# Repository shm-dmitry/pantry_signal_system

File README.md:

This is signal system for pantry.
It will control climate of pantry to smart house.

It will uses autonomous power system
1. car battery on 12v
2. temporary Li-Ion battary on 12v for charging primary battery
3. internal battery (6V..15V) which will used in case of primary and reserve 12V battery discharged. Used to send power alarm to smart house
4. Auto battary hot switch
5. Control over-discharge of all batteries
6. Provide information of current voltage to controller
7. Small current consumption. I plan to charge main battary once per ~6 month. 

It will collect and send next information (incl alarms):
1. Inside flooding alarm
2. Outside flooding alarm
3. Inside humidity level
4. Inside temperature
5. Inside light level
6. Open door alarm
7. Current voltage of all batteries
8. Current battery in use
9. Both 12V batteries discharged alarm 

It will automatically switch on air-drier basing on humidity level

It will have air fan system
1. Manual swotch on
2. Manual swotch off
3. Auto switch off after ~20 minutes

It will send all collected information to smart house system using LoRa channel

Project status

| Hardware | Status |
| --- | --- |
| Supply module | OK |
| Supply module :: Supply controller | OK |
| Logic module :: Flooding sensors | OK |
| Logic module :: Light sensor | OK |
| Logic module :: display | OK |
| Logic module :: humidity and temperature | OK |
| Logic module :: air dryer | OK |
| Logic module :: LoRa transmitter | OK |
| Logic module :: Open door alarm | OK |
| Logic module :: Wakeup button | OK |
| Air fan module | OK |
| LoRa receiver and smart house integration | OK |

| Firmware | Status |
| --- | --- |
| Supply controller | OK |
| Logic controller :: flooding sensors | OK |
| Logic controller :: light sensor | OK |
| Logic controller :: display | OK |
| Logic controller :: humidity and temperature | OK |
| Logic controller :: air dryer | OK |
| Logic controller :: LoRa transmitter | OK |
| Logic controller :: Open door alarm | OK |
| Logic controller :: Wakeup button and deep sleep mode | OK |
| Logic controller :: Integration with supply controller | OK |
| LoRa receiver and smart house integration | OK |

| Board | Status |
| --- | --- |
| Supply board | OK |
| logic module board | OK |
| fan board | OK |
| LoRa Receiver | OK |

| 3D models | Status |
| --- | --- |
| Supply board box | OK |
| Logic model box | OK |
| Air dryer | OK |
| Fan box | OK |
| Fan air intake | OK |
| LoRa receiver box | no |

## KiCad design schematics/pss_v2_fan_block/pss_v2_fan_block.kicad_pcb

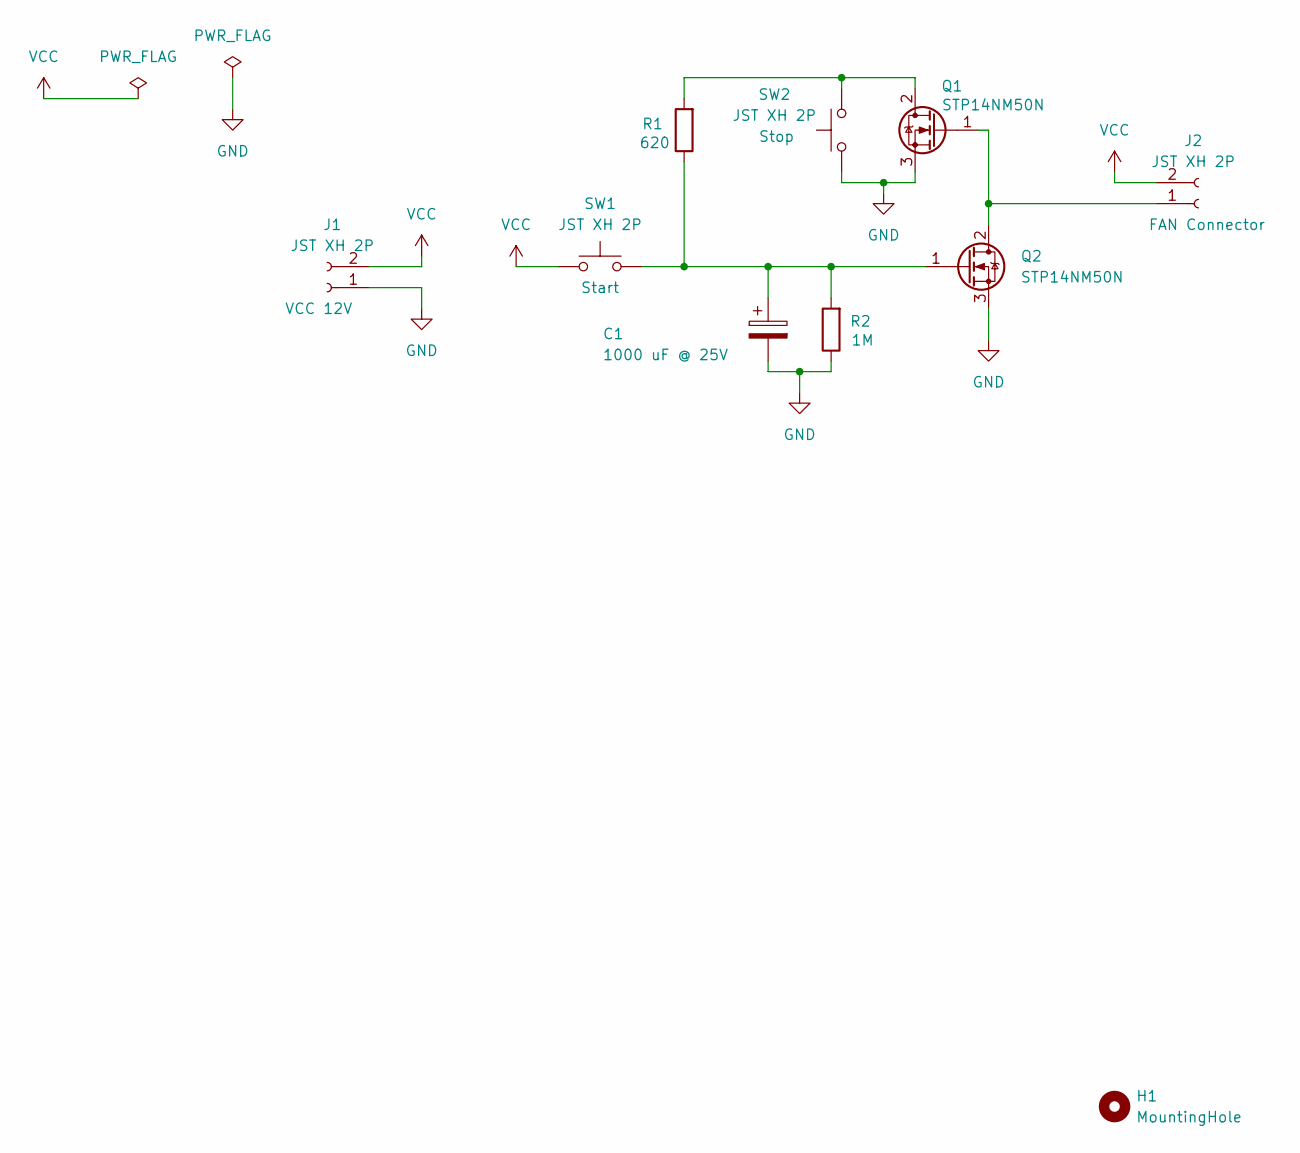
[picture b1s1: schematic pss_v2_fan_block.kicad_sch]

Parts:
C1: 1000 uF @ 25V; CP_Radial_D10.0mm_P5.00mm
H1: MountingHole; MountingHole_2.2mm_M2
J1, J2: JST XH 2P; JST_XH_B2B-XH-A_1x02_P2.50mm_Vertical
Q1, Q2: STP14NM50N; TO-220-3_Vertical
R1: 620; R_0805_2012Metric
R2: 1M; R_0805_2012Metric
SW1, SW2: JST XH 2P; JST_XH_B2B-XH-A_1x02_P2.50mm_Vertical

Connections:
GND: C1.2, J1.1, Q1.3 (S), Q2.3 (S), R2.1, SW2.1
unnamed: J2.1, Q1.1 (G), Q2.2 (D)
unnamed: Q1.2 (D), R1.2, SW2.2
unnamed: C1.1, Q2.1 (G), R1.1, R2.2, SW1.2
VCC: J1.2, J2.2, SW1.1

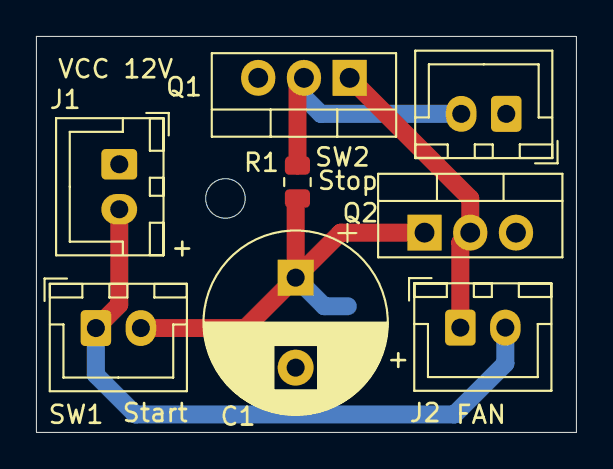
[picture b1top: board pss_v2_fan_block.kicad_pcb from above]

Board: 2 copper layers, 30.0 x 22.0 mm, 10 parts (1 on the bottom side), 5 nets.

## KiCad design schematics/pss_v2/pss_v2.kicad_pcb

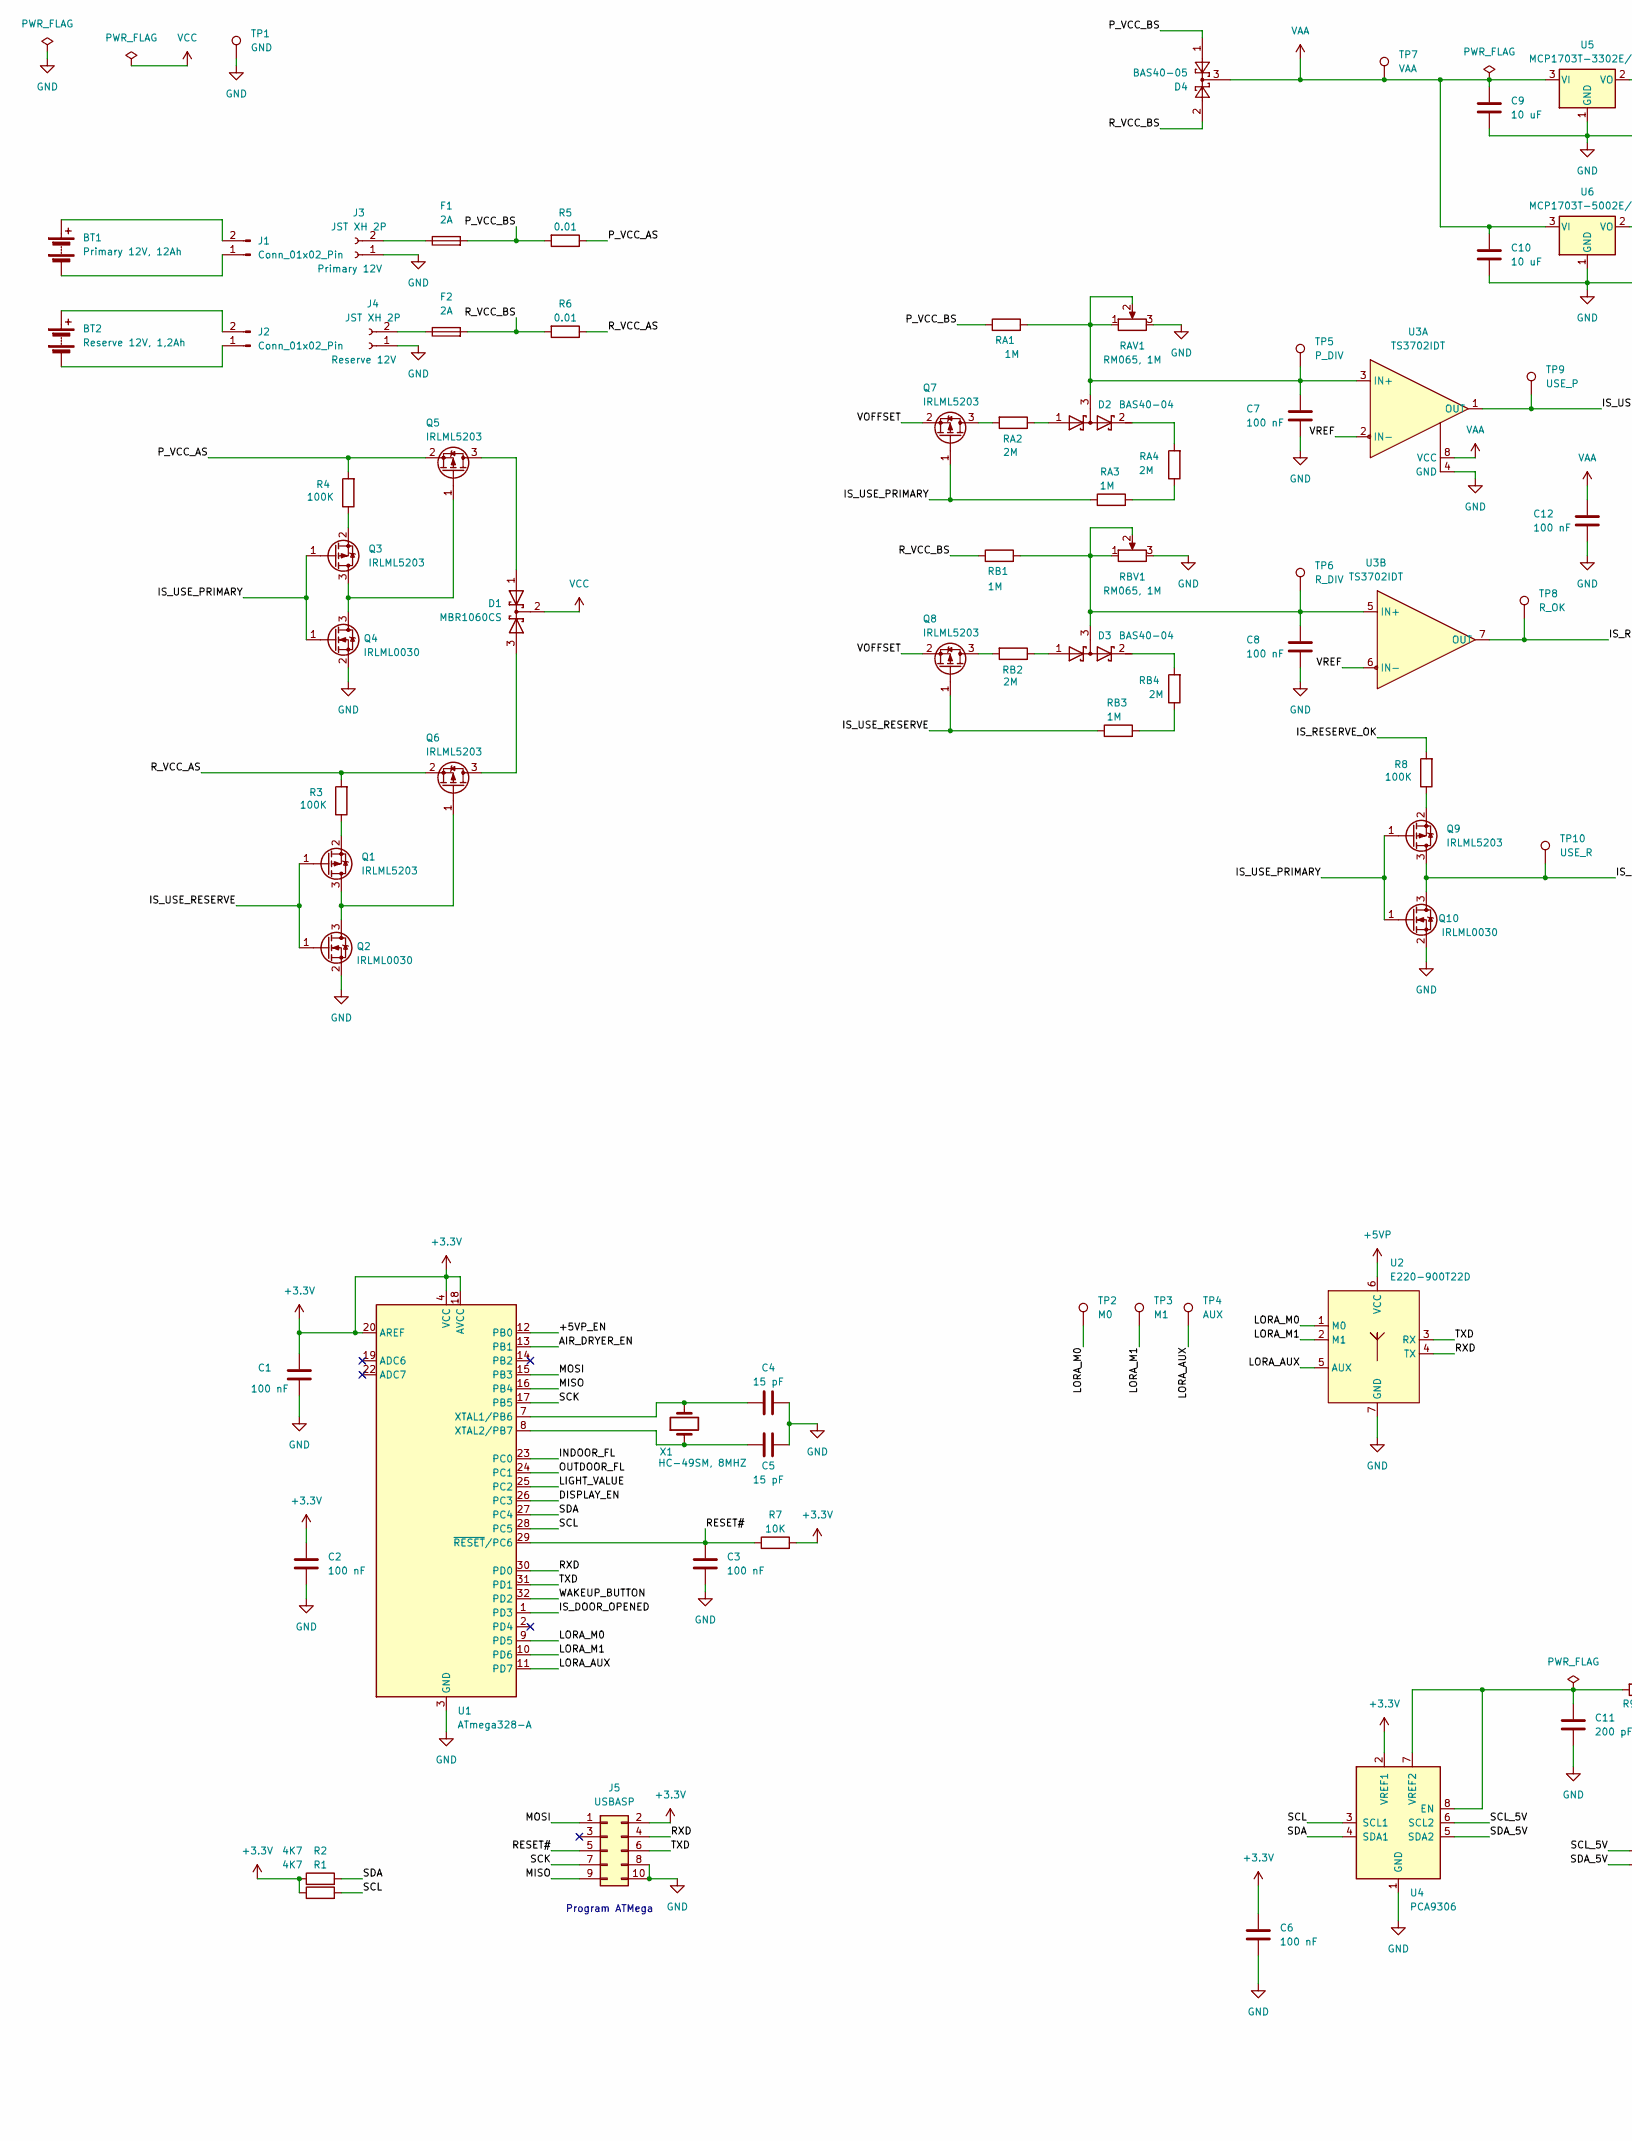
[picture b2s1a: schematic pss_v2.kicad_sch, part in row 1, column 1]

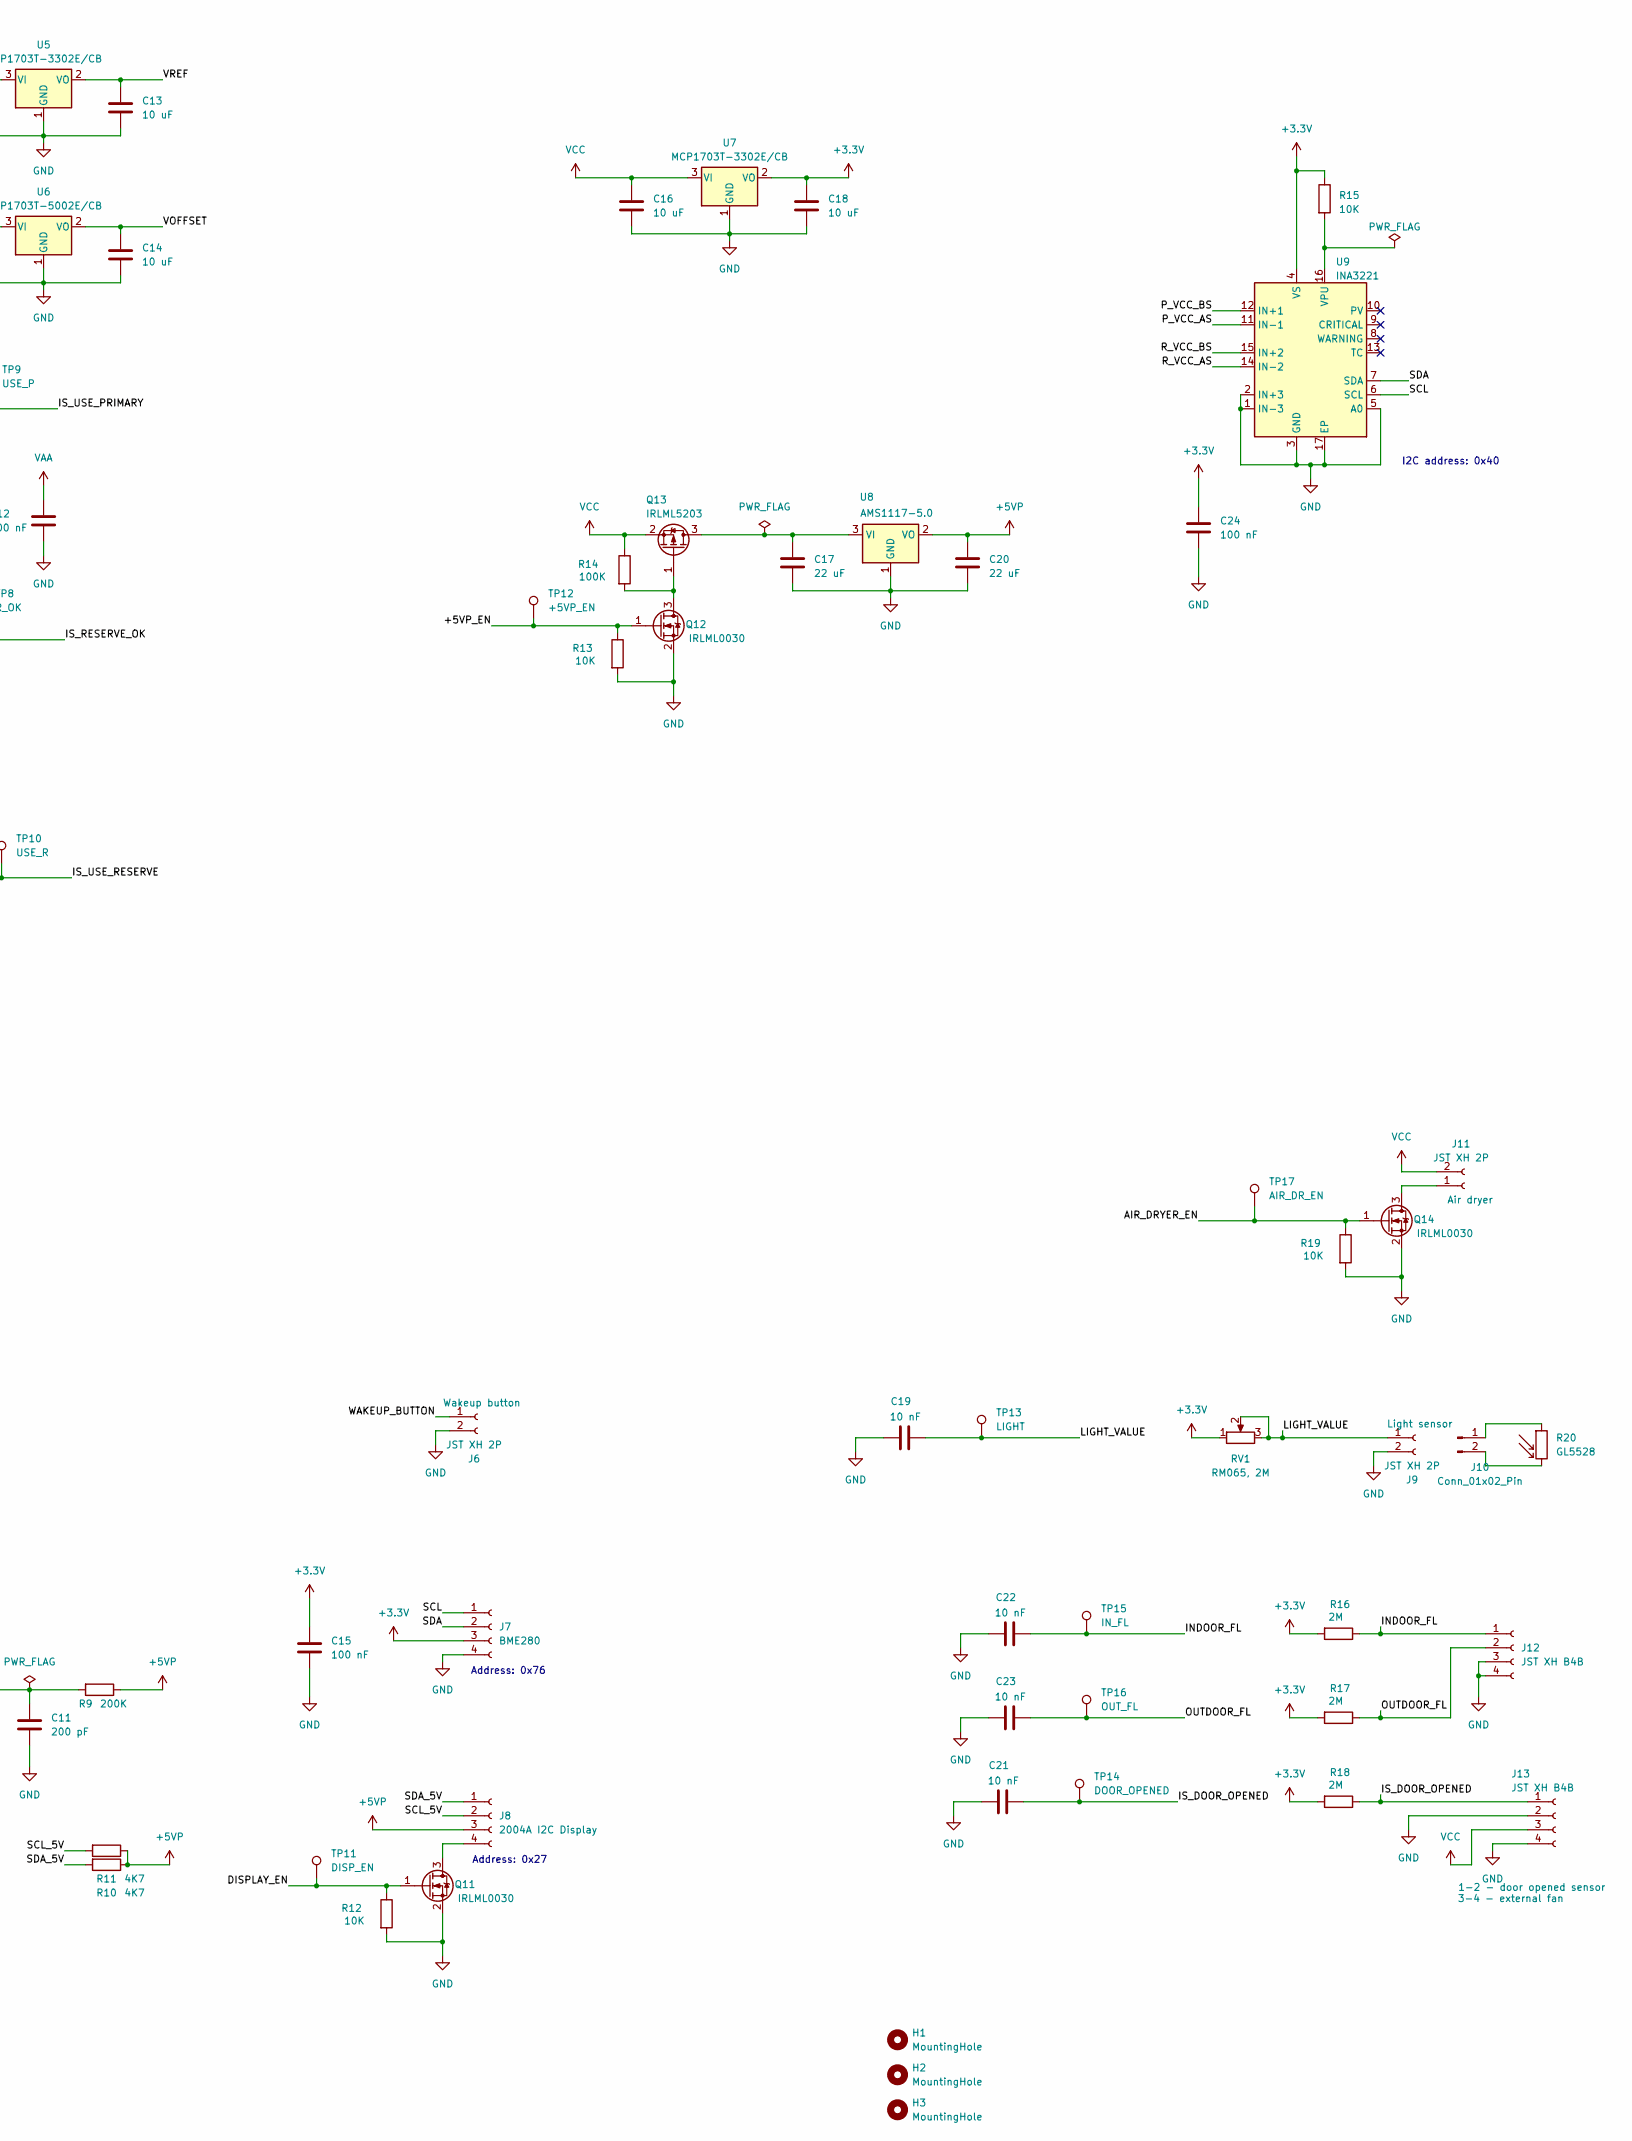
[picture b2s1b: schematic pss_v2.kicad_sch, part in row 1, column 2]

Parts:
BT1: Primary 12V, 12Ah
BT2: Reserve 12V, 1,2Ah
C1, C2, C3, C6, C7, C8, C12, C15, C24: 100 nF; C_0603_1608Metric
C4, C5: 15 pF; C_0603_1608Metric
C9, C10, C13, C14, C16, C18: 10 uF; C_0603_1608Metric
C11: 200 pF; C_0603_1608Metric
C17, C20: 22 uF; C_1210_3225Metric
C19, C21, C22, C23: 10 nF; C_0603_1608Metric
D1: MBR1060CS; TO-252-2
D2, D3: BAS40-04; SOT-23
D4: BAS40-05; SOT-23
F1, F2: 2A; FuseHolder1808
H1, H2, H3: MountingHole; MountingHole_2.2mm_M2
J1, J2, J10: Conn_01x02_Pin
J3, J4, J6, J9, J11: JST XH 2P; JST_XH_B2B-XH-A_1x02_P2.50mm_Vertical
J5: USBASP; DC3-2x05_p2.54
J7: BME280; JST_XH_B4B-XH-A_1x04_P2.50mm_Vertical
J8: 2004A I2C Display; JST_XH_B4B-XH-A_1x04_P2.50mm_Vertical
J12, J13: JST XH B4B; JST_XH_B4B-XH-A_1x04_P2.50mm_Vertical
Q1, Q3, Q5, Q6, Q7, Q8, Q9, Q13: IRLML5203; SOT-23
Q2, Q4, Q10, Q11, Q12, Q14: IRLML0030; SOT-23
R1, R2, R10, R11: 4K7; R_0805_2012Metric
R3, R4, R8, R14: 100K; R_0805_2012Metric
R5, R6: 0.01; R_1206_3216Metric
R7, R12, R13, R15, R19: 10K; R_0805_2012Metric
R9: 200K; R_0805_2012Metric
R16, R17, R18: 2M; R_0805_2012Metric
R20: GL5528
RA1, RA3: 1M; R_0805_2012Metric
RA2, RA4: 2M; R_0805_2012Metric
RAV1: RM065, 1M; Potentiometer_Runtron_RM-065_Vertical
RB1, RB3: 1M; R_0805_2012Metric
RB2, RB4: 2M; R_0805_2012Metric
RBV1: RM065, 1M; Potentiometer_Runtron_RM-065_Vertical
RV1: RM065, 2M; Potentiometer_Runtron_RM-065_Vertical
TP1: GND; TestPoint_Plated_Hole_D1.0mm
TP2: M0; TestPoint_Pad_1.5x1.5mm
TP3: M1; TestPoint_Pad_1.5x1.5mm
TP4: AUX; TestPoint_Pad_1.5x1.5mm
TP5: P_DIV; TestPoint_Pad_1.5x1.5mm
TP6: R_DIV; TestPoint_Pad_1.5x1.5mm
TP7: VAA; TestPoint_Pad_1.5x1.5mm
TP8: R_OK; TestPoint_Pad_1.5x1.5mm
TP9: USE_P; TestPoint_Pad_1.5x1.5mm
TP10: USE_R; TestPoint_Pad_1.5x1.5mm
TP11: DISP_EN; TestPoint_Pad_1.5x1.5mm
TP12: +5VP_EN; TestPoint_Pad_1.5x1.5mm
TP13: LIGHT; TestPoint_Pad_1.5x1.5mm
TP14: DOOR_OPENED; TestPoint_Pad_1.5x1.5mm
TP15: IN_FL; TestPoint_Pad_1.5x1.5mm
TP16: OUT_FL; TestPoint_Pad_1.5x1.5mm
TP17: AIR_DR_EN; TestPoint_Pad_1.5x1.5mm
U1: ATmega328-A; TQFP-32_7x7mm_P0.8mm
U2: E220-900T22D; E220-x
U3: TS3702IDT; SOIC-8_3.9x4.9mm_P1.27mm
U4: PCA9306; MSOP-8_3x3mm_P0.65mm
U5, U7: MCP1703T-3302E/CB; SOT-23
U6: MCP1703T-5002E/CB; SOT-23
U8: AMS1117-5.0; SOT-223-3_TabPin2
U9: INA3221; Texas_RGV0016A_VQFN-16-1EP_4x4mm_P0.65mm_EP2.1x2.1mm
X1: HC-49SM, 8MHZ; Crystal_SMD_HC49-SD

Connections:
+3.3V: C1.1, C2.1, C6.2, C15.2, C18.1, C24.2, J5.2, J7.3, R1.1, R2.1, R7.2, R15.1, R16.2, R17.2, R18.2, RV1.1, U1.4 (VCC), U1.6 (VCC), U1.18 (AVCC), U1.20 (AREF), U4.2 (VREF1), U7.2 (VO), U9.4 (VS)
+5VP: C20.2, J8.3, R9.1, R10.1, R11.1, U2.6 (VCC), U8.2 (VO)
/+5VP_EN: Q12.1 (G), R13.1, TP12.1, U1.12 (PB0)
/AIR_DRYER_EN: Q14.1 (G), R19.1, TP17.1, U1.13 (PB1)
/DISPLAY_EN: Q11.1 (G), R12.1, TP11.1, U1.26 (PC3)
/INDOOR_FL: C22.1, J12.1, R16.1, TP15.1, U1.23 (PC0)
/IS_DOOR_OPENED: C21.1, J13.1, R18.1, TP14.1, U1.1 (PD3)
/IS_RESERVE_OK: R8.2, TP8.1, U3.7 (OUT)
/IS_USE_PRIMARY: Q3.1 (G), Q4.1 (G), Q7.1 (G), Q9.1 (G), Q10.1 (G), RA3.1, TP9.1, U3.1 (OUT)
/IS_USE_RESERVE: Q1.1 (G), Q2.1 (G), Q8.1 (G), Q9.3 (D), Q10.3 (D), RB3.1, TP10.1
/LIGHT_VALUE: C19.1, J9.1, RV1.2, RV1.3, TP13.1, U1.25 (PC2)
/LORA_AUX: TP4.1, U1.11 (PD7), U2.5 (AUX)
/LORA_M0: TP2.1, U1.9 (PD5), U2.1 (M0)
/LORA_M1: TP3.1, U1.10 (PD6), U2.2 (M1)
/MISO: J5.9, U1.16 (PB4)
/MOSI: J5.1, U1.15 (PB3)
/OUTDOOR_FL: C23.1, J12.2, R17.1, TP16.1, U1.24 (PC1)
/P_VCC_AS: Q5.2 (S), R4.2, R5.1, U9.11 (IN-1)
/P_VCC_BS: D4.1, F1.2, R5.2, RA1.1, U9.12 (IN+1)
/RESET#: C3.1, J5.5, R7.1, U1.29 (~RESET/PC6)
/RXD: J5.4, U1.30 (PD0), U2.4 (TX)
/R_VCC_AS: Q6.2 (S), R3.2, R6.1, U9.14 (IN-2)
/R_VCC_BS: D4.2, F2.2, R6.2, RB1.1, U9.15 (IN+2)
/SCK: J5.7, U1.17 (PB5)
/SCL: J7.1, R2.2, U1.28 (PC5), U4.3 (SCL1), U9.6 (SCL)
/SCL_5V: J8.2, R10.2, U4.6 (SCL2)
/SDA: J7.2, R1.2, U1.27 (PC4), U4.4 (SDA1), U9.7 (SDA)
/SDA_5V: J8.1, R11.2, U4.5 (SDA2)
/TXD: J5.6, U1.31 (PD1), U2.3 (RX)
/VOFFSET: C14.1, Q7.2 (S), Q8.2 (S), U6.2 (VO)
/VREF: C13.1, U3.2 (IN-), U3.6 (IN-), U5.2 (VO)
/WAKEUP_BUTTON: J6.1, U1.32 (PD2)
GND: C1.2, C2.2, C3.2, C4.2, C5.2, C6.1, C7.2, C8.2, C9.2, C10.2, C11.1, C12.2, C13.2, C14.2, C15.1, C16.2, C17.1, C18.2, C19.2, C20.1, C21.2, C22.2, C23.2, C24.1, J3.1, J4.1, J5.8, J5.10, J6.2, J7.4, J9.2, J12.3, J12.4, J13.2, J13.4, Q2.2 (S), Q4.2 (S), Q10.2 (S), Q11.2 (S), Q12.2 (S), Q14.2 (S), R12.2, R13.2, R19.2, RAV1.3, RBV1.3, TP1.1, U1.3 (GND), U1.5 (GND), U1.21 (GND), U2.7 (GND), U3.4 (GND), U4.1 (GND), U5.1 (GND), U6.1 (GND), U7.1 (GND), U8.1 (GND), U9.1 (IN-3), U9.2 (IN+3), U9.3 (GND), U9.5 (A0), U9.17 (EP)
unnamed: BT1.1 (+), J1.2
unnamed: BT1.2 (-), J1.1
unnamed: BT2.1 (+), J2.2
unnamed: BT2.2 (-), J2.1
unnamed: D2.1 (A), RA2.1
unnamed: D2.2 (K), RA4.2
unnamed: C7.1, D2.3 (common), RA1.2, RAV1.1, RAV1.2, TP5.1, U3.3 (IN+)
unnamed: D3.1 (A), RB2.1
unnamed: D3.2 (K), RB4.2
unnamed: C8.1, D3.3 (common), RB1.2, RBV1.1, RBV1.2, TP6.1, U3.5 (IN+)
unnamed: F1.1, J3.2
unnamed: F2.1, J4.2
unnamed: J8.4, Q11.3 (D)
unnamed: J10.1, R20.1
unnamed: J10.2, R20.2
unnamed: J11.1, Q14.3 (D)
unnamed: Q1.3 (D), Q2.3 (D), Q6.1 (G)
unnamed: Q1.2 (S), R3.1
unnamed: Q3.3 (D), Q4.3 (D), Q5.1 (G)
unnamed: Q3.2 (S), R4.1
unnamed: D1.1 (A), Q5.3 (D)
unnamed: D1.3 (A), Q6.3 (D)
unnamed: Q7.3 (D), RA2.2
unnamed: Q8.3 (D), RB2.2
unnamed: Q9.2 (S), R8.1
unnamed: Q12.3 (D), Q13.1 (G), R14.2
unnamed: C17.2, Q13.3 (D), U8.3 (VI)
unnamed: RA3.2, RA4.1
unnamed: RB3.2, RB4.1
unnamed: C4.1, U1.7 (XTAL1/PB6), X1.2
unnamed: C5.1, U1.8 (XTAL2/PB7), X1.1
unnamed: C11.2, R9.2, U4.7 (VREF2), U4.8 (EN)
unnamed: R15.2, U9.16 (VPU)
VAA: C9.1, C10.1, C12.1, D4.3, TP7.1, U3.8 (VCC), U5.3 (VI), U6.3 (VI)
VCC: C16.1, D1.2 (K), J11.2, J13.3, Q13.2 (S), R14.1, U7.3 (VI)

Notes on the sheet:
Address: 0x27
Program ATMega
I2C address: 0x40
Address: 0x76

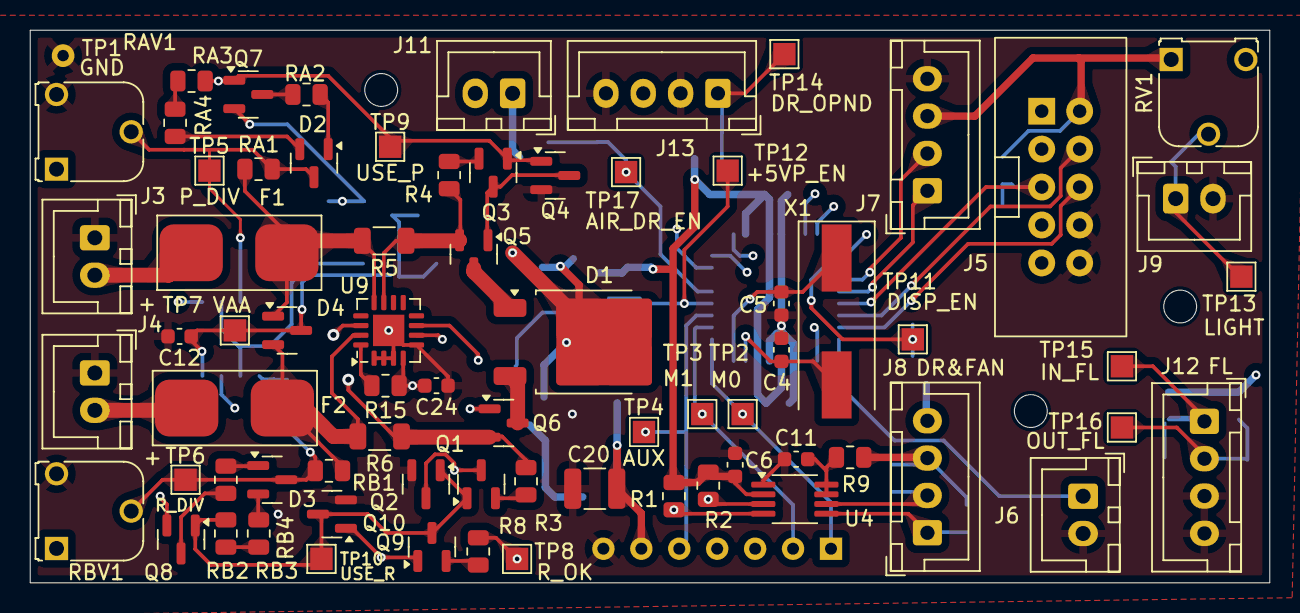
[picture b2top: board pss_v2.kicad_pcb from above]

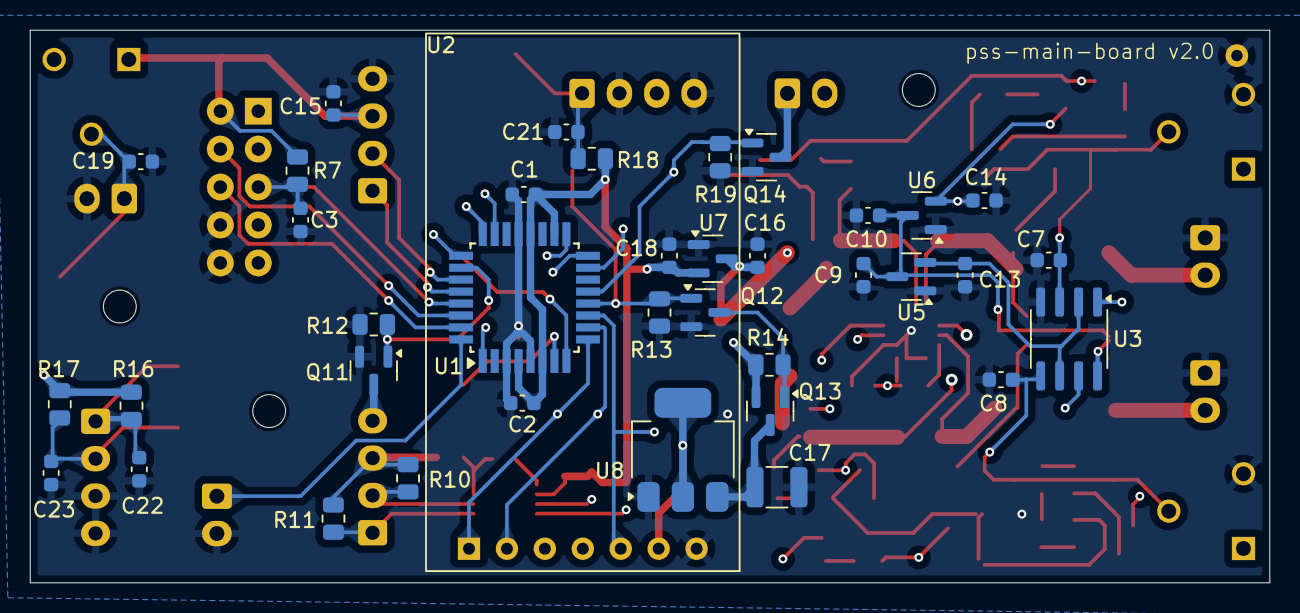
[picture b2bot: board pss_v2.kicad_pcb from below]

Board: 4 copper layers, 83.0 x 37.0 mm, 114 parts (38 on the bottom side), 62 nets.

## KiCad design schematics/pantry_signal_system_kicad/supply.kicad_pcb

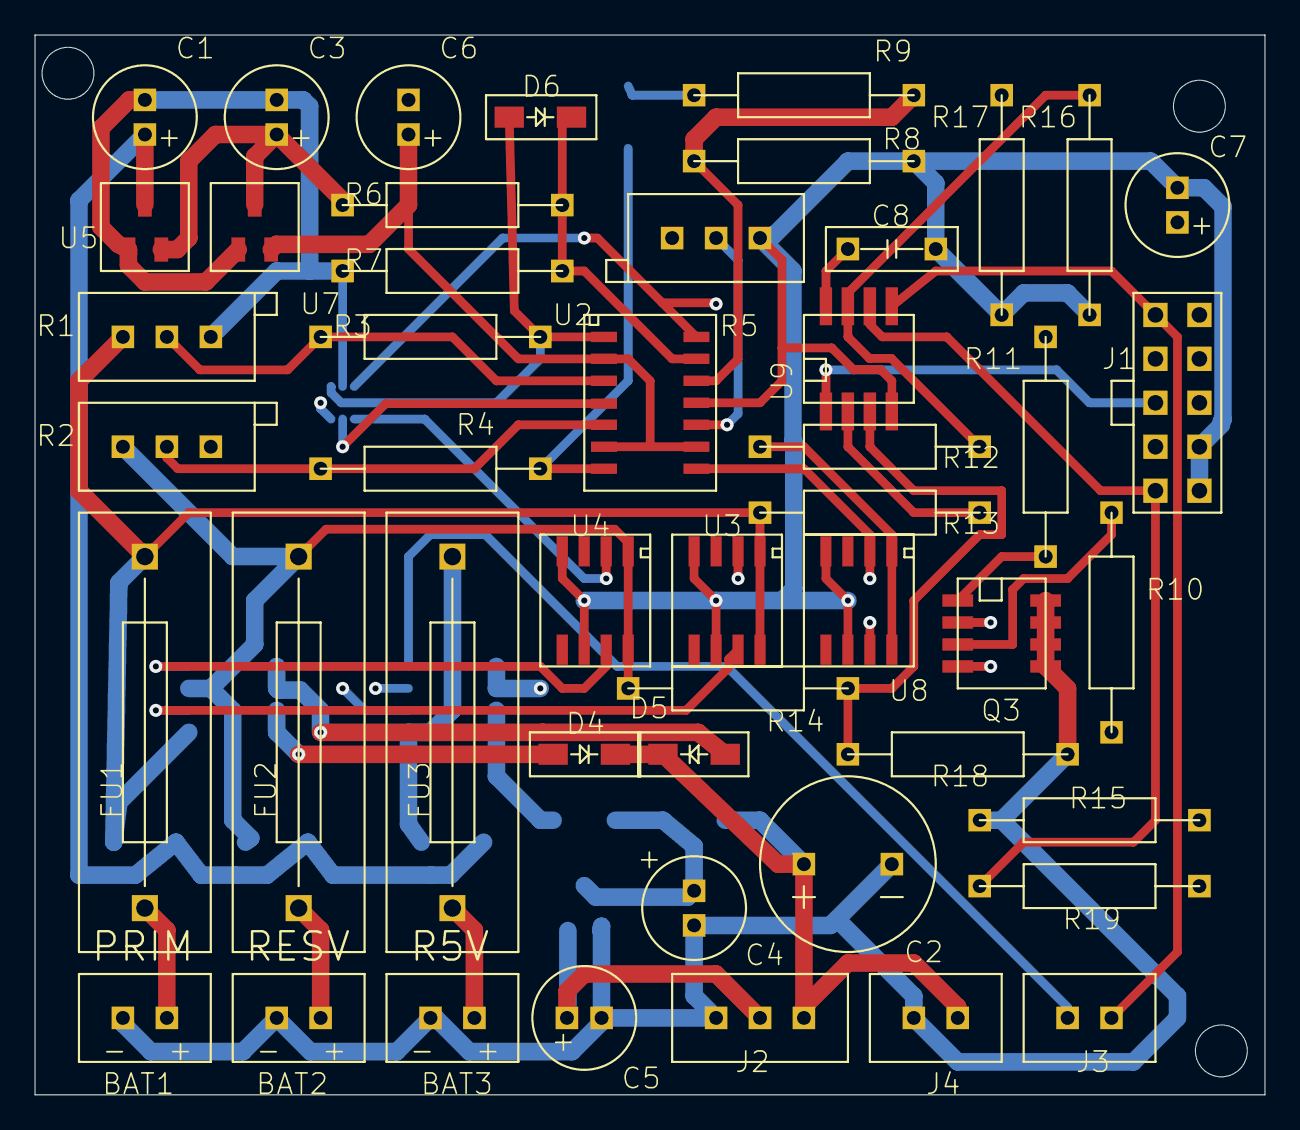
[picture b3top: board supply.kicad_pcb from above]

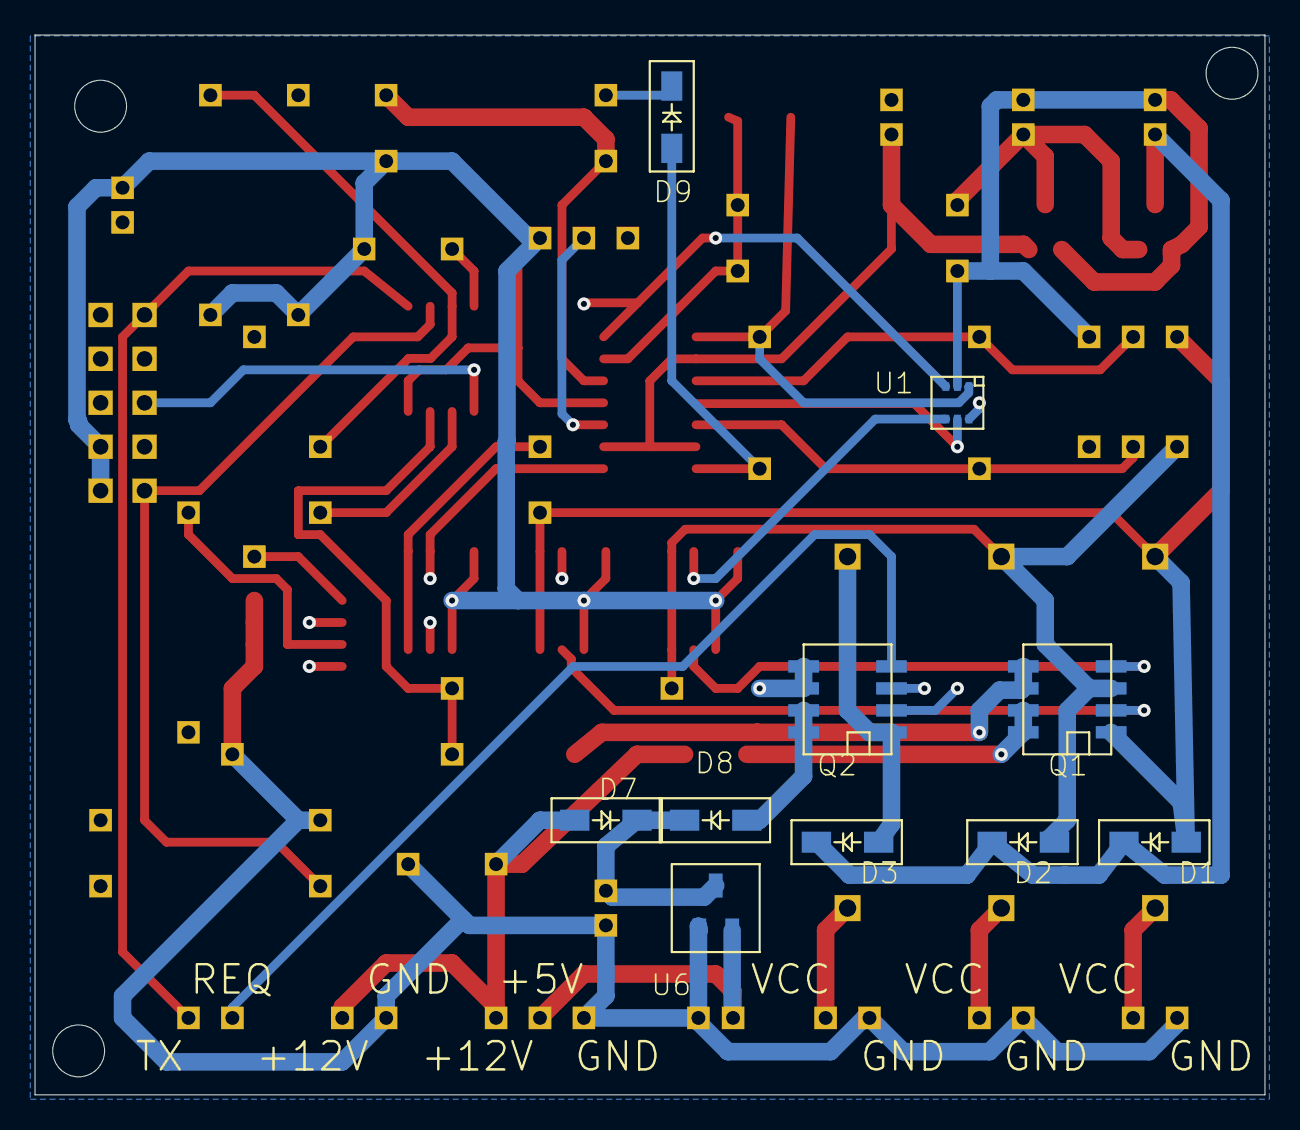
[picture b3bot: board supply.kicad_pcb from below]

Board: 4 copper layers, 71.1 x 61.3 mm, 61 parts (10 on the bottom side), 42 nets.

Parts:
@HOLE0, @HOLE1, @HOLE2: (no value)
BAT1, BAT2: 12V ... 15V; BATTERY
BAT3: 10V ... 15V; BATTERY
C1, C3, C4, C5, C6, C7: 10 uF; C-MINI-5X7
C2: 1000 uF; C
C8: 0.1 uF; C-1
D1, D2, D3, D4, D5, D6, D7, D8, D9: MBR130LSFT1G; D-SOD-123FL
FU1, FU2: H520PT / 1A; FU
FU3: H520PT / 0.5A; FU
J1: USBASP_PIN
J2: JST-XH254-3P
J3, J4: JST-XH254-2P
Q1, Q2, Q3: FDS4935A; SO-8
R1, R2, R5: 2M; RD-3296W-1-205LF
R3, R4, R6, R8, R9, R12, R13, R14: 2M; R
R7, R16, R17, R18: 1M; R
R10, R15: 10K; R
R11: 3K; R
R19: 620; R
U1: NC7WZ04; SC70
U2: AD8544SO-14; SO-14
U3, U4, U8: FAN73611; SOIC-8
U5, U6: MCP1703T-5002E/CB; SOT-23A
U7: MCP1703T-3302E/CB; SOT-23A
U9: ATTINY13SO-8-209; SO-8-209

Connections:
+5V: C5.PLUS, J2.PIN2, Q2.P3, U6.P2
+12V: C2.PIN_PLUS, D4.CATHODE, D5.CATHODE, D7.ANODE, J2.PIN1, J4.PIN2, R5.P2
BAT1: BAT1.PLUS, FU1.P$1
BAT2: BAT2.PLUS, FU2.P$1
BAT3: BAT3.PLUS, FU3.P$1
CURRENT_SUPPLY_IN_USE: J1.MISO, R19.P$2, U9.P6
GND: BAT1.MINUS, BAT2.MINUS, BAT3.MINUS, C1.MINUS, C2.PIN_GND, C3.MINUS, C4.MINUS, C5.MINUS, C6.MINUS, C7.MINUS, C8.P$2, J1.GND, J1.GND1, J2.PIN3, J4.PIN1, Q3.P5, Q3.P6, Q3.P7, Q3.P8, R1.P2, R2.P2, R5.P1, R7.P$1, R8.P$2, R15.P$1, R16.P$1, R17.P$1, R18.P$1, U1.P2, U2.P11, U3.P_4, U3.P_6, U4.P_4, U4.P_6, U5.P1, U6.P1, U7.P1, U8.P_4, U8.P_6, U9.P4
IS_12V_POWER_OK: R5.P3, U2.P10
IS_ENABLE_RESERVE_+5V_INV: Q3.P2, U2.P8, U8.P_2
IS_PRIMARY_BATTERY_OK: D6.ANODE, R3.P$2, U1.P1, U2.P1
IS_RESERVE_BATTERY_OK: D9.ANODE, R4.P$1, U2.P7
IS_USE_RESERVE_BATTERY: Q3.P4, U1.P3, U2.P14
unnamed: C1.PLUS, D1.CATHODE, D2.CATHODE, D3.CATHODE, U5.P3
unnamed: D6.CATHODE, R6.P$2, R7.P$2, U2.P13
unnamed: R1.P3, R3.P$1, U2.P3
unnamed: C4.PLUS, D7.CATHODE, D8.CATHODE, U6.P3
unnamed: R2.P3, R4.P$2, U2.P5
unnamed: R8.P$1, R9.P$1, U2.P12
unnamed: D4.ANODE, Q1.P7, Q1.P8
unnamed: D5.ANODE, Q1.P5, Q1.P6
unnamed: J1.RST, U9.P1
unnamed: U1.P6, U3.P_2
unnamed: U1.P4, U4.P_2
unnamed: Q3.P3, R10.P$1
unnamed: D8.ANODE, Q2.P7, Q2.P8
unnamed: Q3.P1, R11.P$1
unnamed: D9.CATHODE, R9.P$2
unnamed: C7.PLUS, R10.P$2, R11.P$2, R15.P$2, R19.P$1
PRIMARY_SUPPLY_12V: D1.ANODE, FU1.P$2, Q1.P1, R1.P1, R13.P$2, U3.P_1, U3.P_8
PRIMARY_VOLTAGE_LEVEL: R13.P$1, R17.P$2, U9.P2
REQUEST_SUPPLY_MEASURE_INV: J3.PIN2, Q2.P4
RESERVE_+5V_LEVEL: J1.SCK, R12.P$1, R16.P$2, U9.P7
RESERVE_+5V_SUPPLY: D3.ANODE, FU3.P$2, Q2.P1, R12.P$2, U8.P_1, U8.P_8
RESERVE_SUPPLY_12V: D2.ANODE, FU2.P$2, Q1.P3, R2.P1, R14.P$2, U4.P_1, U4.P_8
RESERVE_VOLTAGE_LEVEL: R14.P$1, R18.P$2, U9.P3
SUPPLY_AVR_+5V: C8.P$1, J1.VCC, Q2.P5, Q2.P6, U9.P8
SUPPLY_CONTROL_3V3: C6.PLUS, U2.P2, U2.P6, U2.P9, U7.P2
SUPPLY_CONTROL_+5V: C3.PLUS, R6.P$1, U1.P5, U2.P4, U5.P2, U7.P3
SUPPLY_UART_TX: J1.MOSI, J3.PIN1, U9.P5
USE_PRIMARY_BATTERY: Q1.P2, U3.P_7
USE_RESERVE_5V_BATTERY: Q2.P2, U8.P_7
USE_RESERVE_BATTERY: Q1.P4, U4.P_7

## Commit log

2021-11-15 Initial
2021-11-15 Start creating schema
2021-11-15 Initial schema for supply subsystem
2021-11-16 Initial schema for logic module
2021-11-16 Initial schema for fan system
2021-11-16 added some nominals
2021-11-20 Added +5V reserve supply and auto-enable schema wich switched it on when primary and reserve 12V supply discharged
2021-11-20 Update library
2021-11-20 Added nominals for air fan
2021-11-20 Fixed comment for working time of air fan
2021-11-21 Start writing firmware for logic module
2021-11-21 open door alarm
2021-11-25 changed mosfet drivers to FAN73611
2021-11-25 Added lora-send code
2021-11-25 LoRa - added configuration, and wakeup-sleep-mode
2021-12-02 3D model for SOIC8-chips adapter
2021-12-03 Finalized debug model for SOIC8 chips
2021-12-03 Added model for SOC32A debug adapter (bottom side)
2021-12-03 added topside model for SOC23A debug adapter
2021-12-09 Air drier schema works
2021-12-10 Lora module FW and HW works. Encrypted connection betweed modules estabilished
2021-12-11 Added firmware for supply module (not tested yet)
2021-12-12 Display driver and schema ready
2021-12-12 Light sensor is ready now
2021-12-12 Start working under supply schema
2021-12-12 Added programmer connector for ATTiny
2021-12-13 Added integration with supply avr module (not tested yet)
2022-01-12 Working under supplu control
2022-01-12 Continue working under supply control schematics. Changed N-channel mosfets to P-channel mosfets. Small changes in logic control module
2022-01-15 Continue working under supply schematics and supply controller firmware
2022-01-15 actual library
2022-01-16 working under supply schematics. I think I solved problem with 'current battery in use' signal reading
2022-01-18 and another iteration for suplly avr data reading
2022-01-25 Supply controller schematics and firmware ready
2022-01-26 working under supply schematics
2022-01-31 I finished supply control schematics
2022-02-01 start working under wakeup button and deep sleep mode
2022-02-01 Initial deepsleep impl
2022-02-02 1. BME280 works fine. 2. I have problem with I2C bus when display connected, but unpowerd. I will investigate this problem
2022-02-03 Added 3D model of air dryer
2022-02-03 renamed stl file
2022-02-03 remove deleted file
2022-02-08 Try to fix problem with I2C bus and display module
2022-02-08 PINs in source code assigned as in schematics
2022-02-09 wakeup button, deepsleep & display works fine
2022-02-09 ADded lora receiver schema
2022-02-09 Start project LoRa receiver
2022-02-10 lora receiver - finished ESP32 firmware (not tested yet)
2022-02-10 added secret header file to gitignore to ensure I will not push it later
2022-02-10 move secrets to one file
2022-02-10 exclude new secrets file from git
2022-02-10 Fix problem with signal level 3V3 <-> 5V for lora
2022-02-11 Preparing primary schema for creating board - all packages setup
2022-02-13 Changed LoRa Receiver schematics to use level converter modules
2022-02-13 Added board for LoRa receiver
2022-02-13 Added FAN Control board
2022-02-13 Added Logic Module board
2022-02-13 Added supply board
2022-02-14 Boards checked, some packages changed, library synced with this project
2022-02-14 I submited order for this boards....
2022-02-14 Fixed issue in air dryer container 3D model
2022-02-14 air fan income - initial version, I will reduce it's size later
2022-02-15 Air Fan Income redesigned
2022-02-15 Added Air Fan Outcome 3D model
2022-03-03 3D models for air income and air dryer
2022-03-19 1. Fixed issues in boards and firmwares
2022-03-19 Actual board
2022-03-22 Added 3D Models for boxes
2022-04-04 Preparing to assemble device
2022-04-04 Changes in library
2022-04-04 Fixed issue with connection between supply and logic module
2022-04-20 Changes in schematics, changes in source code. Current version works too, but I changed boards to fix some possible errors
2022-04-20 changed gitignore to ensure my private keys didnt pushed
2022-04-20 Secrets moved to another un-tracked header file
2022-06-24 Debugging logic module firmware, estabilishing LoRa connection....
2022-07-01 Firmware for logic-control module finished
2022-07-01 Capacitor nominal changed in logic-module to fix problem with chip restart when LoRa sends data with high current consumption
2022-07-20 working under 3d models
2022-07-25 working under 3D model
2022-07-25 Changes in 3D model
2022-12-06 Changed 3D models to actuall printed, changed firmware to actually flushed
2024-03-07 project finished
2024-10-17 save latest changes before starting v2
2024-10-25 pss v2 board
2024-10-25 fan switch schema rewrited to kicad
